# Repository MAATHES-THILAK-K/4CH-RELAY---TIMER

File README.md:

# 4CH Relay Timer

## Overview
ESP32-C3 based 4-channel relay controller with DS3231 RTC for timer applications. Each channel handles 10A AC loads with MOSFET input control.

## Features
- 4x 10A relays with MOSFET control
- ESP32-C3 Mini for Wi-Fi/Bluetooth
- DS3231 RTC for precise timing
- Direct AC input sensing
- Timer-based automation

## Hardware
- MCU: ESP32-C3-MINI-1
- RTC: DS3231 with battery backup
- Relays: 10A 250VAC SPDT
- Input: 5V DC
- AC sensing: Opto-isolated

## Usage
1. Power with 5V DC
2. Connect AC loads to relay outputs
3. Program via USB-C
4. Set timers via web interface

## Safety
⚠️ **HIGH VOLTAGE** - Requires proper insulation and qualified installation.

## License
Apache 2.0

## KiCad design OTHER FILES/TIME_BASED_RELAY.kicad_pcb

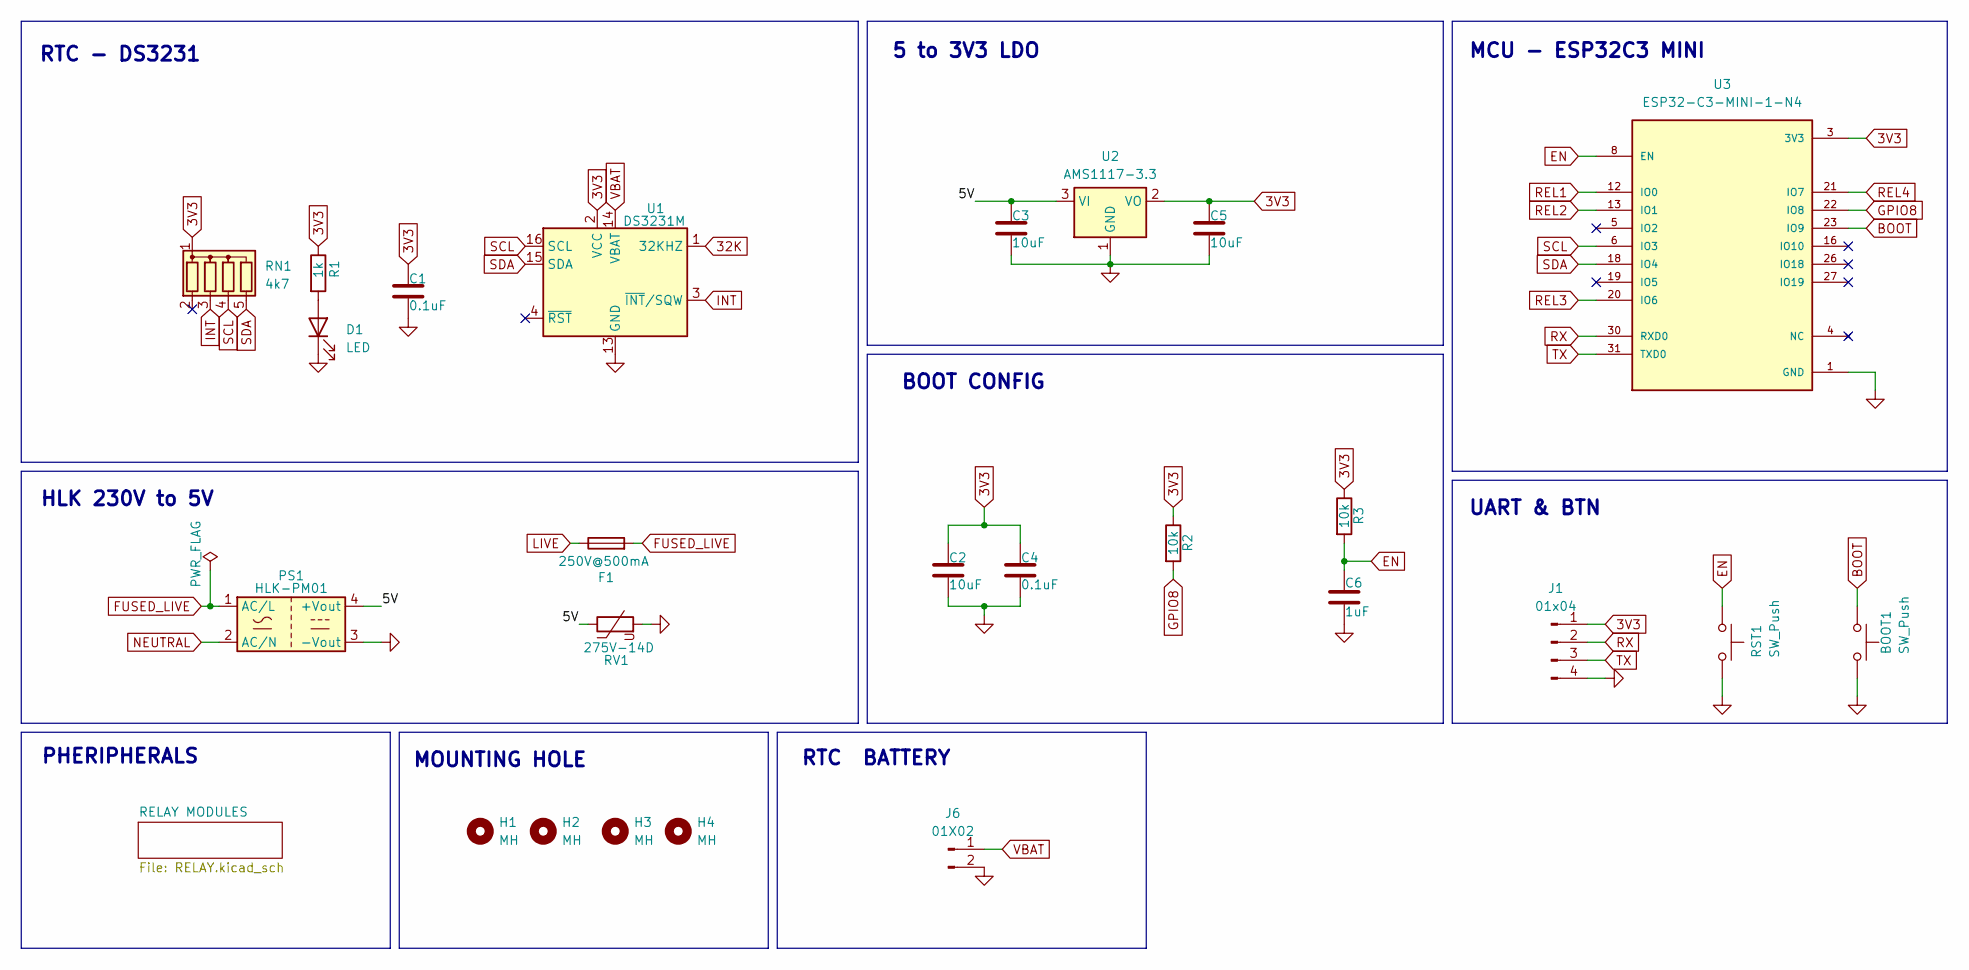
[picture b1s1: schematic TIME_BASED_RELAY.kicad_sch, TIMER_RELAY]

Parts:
BOOT1: SW_Push; SW_Tactile_SPST_NO_Straight_CK_PTS636Sx25SMTRLFS
C1, C4: 0.1uF; C_0805_2012Metric_Pad1.18x1.45mm_HandSolder
C2, C3, C5: 10uF; C_0805_2012Metric_Pad1.18x1.45mm_HandSolder
C6: 1uF; C_0805_2012Metric_Pad1.18x1.45mm_HandSolder
D1: LED; LED_0805_2012Metric_Pad1.15x1.40mm_HandSolder
F1: 250V@500mA; Fuseholder_Clip-6.3x32mm_Littelfuse_102_122_Inline_P34.21x7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
H1, H2, H3, H4: MH; MountingHole_2.2mm_M2_Pad_Via
J1: 01x04; JST_SH_SM04B-SRSS-TB_1x04-1MP_P1.00mm_Horizontal
J6: 01X02; BatteryHolder_Keystone_1058_1x2032
PS1: HLK-PM01; Converter_ACDC_Hi-Link_HLK-PMxx
R1: 1k; R_0805_2012Metric_Pad1.20x1.40mm_HandSolder
R2, R3: 10k; R_0805_2012Metric_Pad1.20x1.40mm_HandSolder
RN1: 4k7; R_Array_SIP5
RST1: SW_Push; SW_Tactile_SPST_NO_Straight_CK_PTS636Sx25SMTRLFS
RV1: 275V-14D; RV_Disc_D15.5mm_W7.5mm_P7.5mm
U1: DS3231M; SOIC-16W_7.5x10.3mm_P1.27mm
U2: AMS1117-3.3; SOT-223-3_TabPin2
U3: ESP32-C3-MINI-1-N4; XCVR_ESP32-C3-MINI-1-N4; PARTREV v1.0

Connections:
3V3: C1.1, C2.1, C4.1, C5.1, J1.1, R1.1, R2.1, R3.1, RN1.1 (common), U1.2 (VCC), U2.2 (VO), U3.3 (3V3)
32K: U1.1 (32KHZ)
/5V: C3.1, PS1.4 (+Vout), RV1.1, U2.3 (VI)
BOOT: BOOT1.1, U3.23 (IO9)
EN: C6.1, R3.2, RST1.1, U3.8 (EN); also elsewhere on the board
FUSED_LIVE: F1.2, PS1.1 (AC/L)
GND: BOOT1.2, C1.2, C2.2, C3.2, C4.2, C5.2, C6.2, D1.1 (K), J1.4, J6.2, PS1.3 (-Vout), RST1.2, RV1.2, U1.5 (GND), U1.6 (GND), U1.7 (GND), U1.8 (GND), U1.9 (GND), U1.10 (GND), U1.11 (GND), U1.12 (GND), U1.13 (GND), U2.1 (GND), U3.1 (GND), U3.2 (GND), U3.11 (GND), U3.14 (GND), U3.36 (GND), U3.37 (GND), U3.38 (GND), U3.39 (GND), U3.40 (GND), U3.41 (GND), U3.42 (GND), U3.43 (GND), U3.44 (GND), U3.45 (GND), U3.46 (GND), U3.47 (GND), U3.48 (GND), U3.49_1 (GND), U3.49_2 (GND), U3.49_3 (GND), U3.49_4 (GND), U3.49_5 (GND), U3.49_6 (GND), U3.49_7 (GND), U3.49_8 (GND), U3.49_9 (GND), U3.50 (GND), U3.51 (GND), U3.52 (GND), U3.53 (GND); also elsewhere on the board
GPIO8: R2.2, U3.22 (IO8)
INT: RN1.3 (R2), U1.3 (~INT/SQW)
LIVE: F1.1; also elsewhere on the board
NEUTRAL: PS1.2 (AC/N); also elsewhere on the board
unnamed: D1.2 (A), R1.2
REL1: U3.12 (IO0); also elsewhere on the board
REL2: U3.13 (IO1); also elsewhere on the board
REL3: U3.20 (IO6); also elsewhere on the board
REL4: U3.21 (IO7); also elsewhere on the board
RX: J1.2, U3.30 (RXD0)
SCL: RN1.4 (R3), U1.16 (SCL), U3.6 (IO3)
SDA: RN1.5 (R4), U1.15 (SDA), U3.18 (IO4)
TX: J1.3, U3.31 (TXD0)
VBAT: J6.1, U1.14 (VBAT)

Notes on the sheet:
PHERIPHERALS
HLK 230V to 5V
RTC BATTERY
MOUNTING HOLE
UART & BTN
BOOT CONFIG
MCU - ESP32C3 MINI
RTC - DS3231
5 to 3V3 LDO

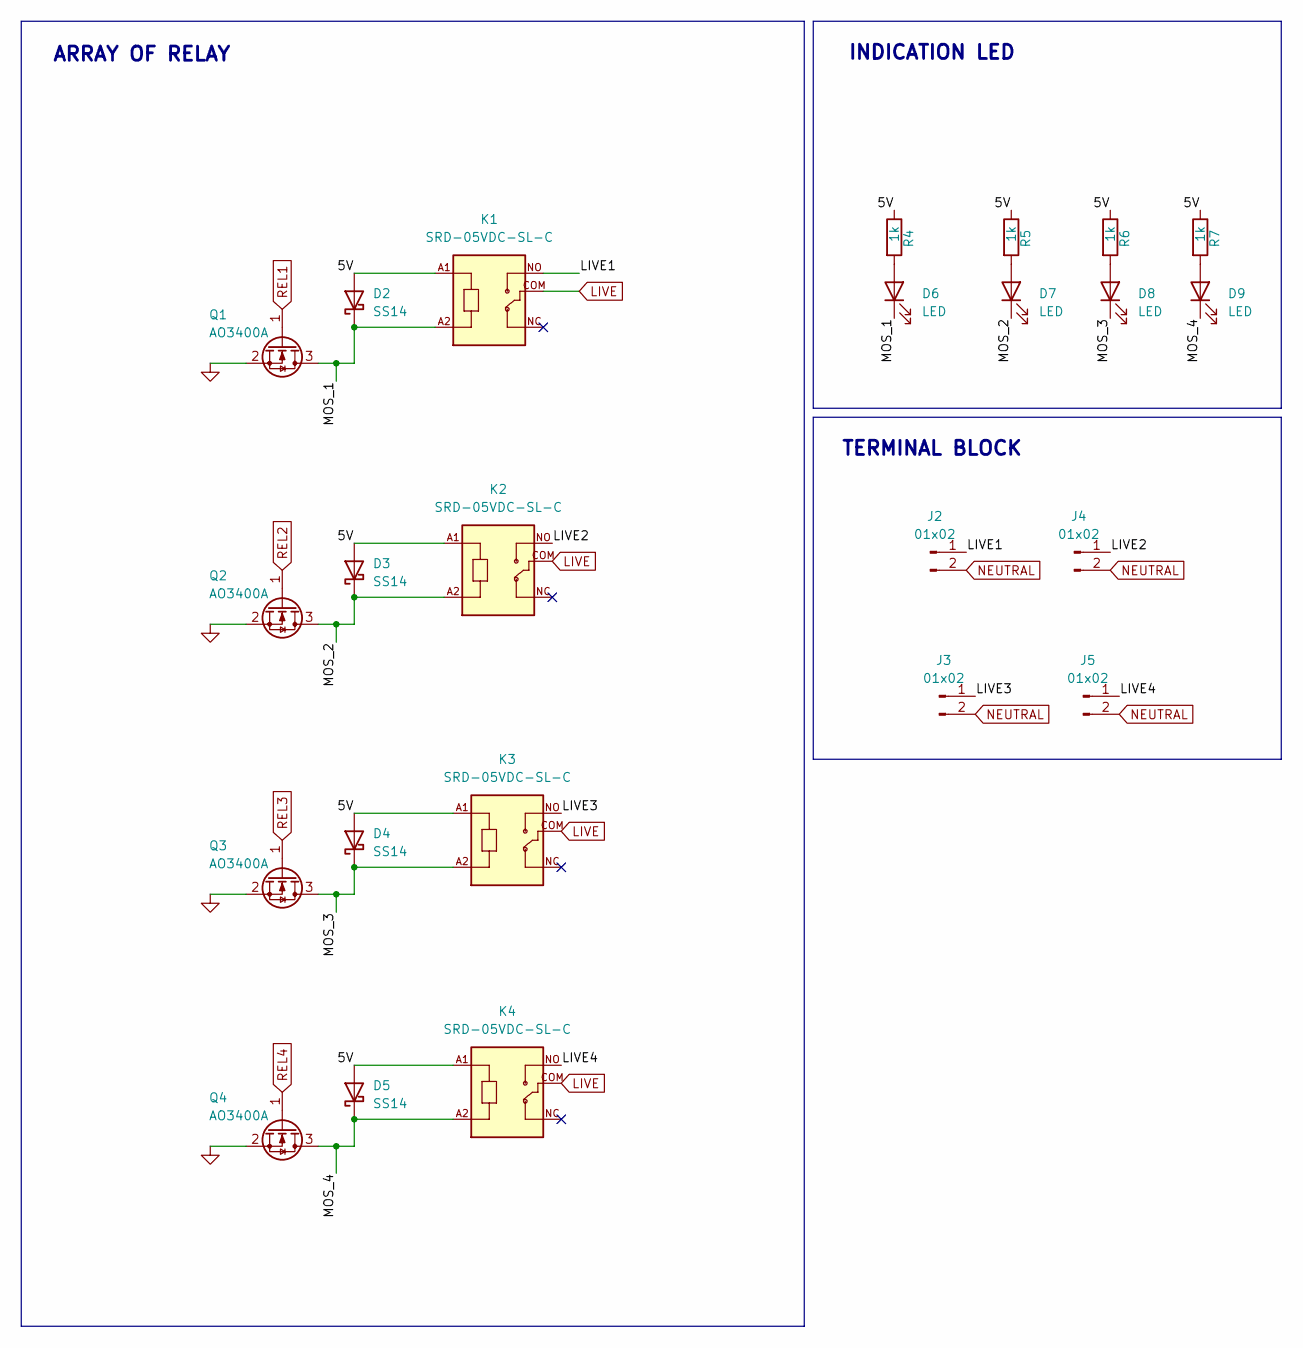
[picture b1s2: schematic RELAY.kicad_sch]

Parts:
D2, D3, D4, D5: SS14; D_SMA
D6, D7, D8, D9: LED; LED_0805_2012Metric_Pad1.15x1.40mm_HandSolder
J2, J3, J4, J5: 01x02; TerminalBlock_MaiXu_MX126-5.0-02P_1x02_P5.00mm
K1, K2, K3, K4: SRD-05VDC-SL-C; RELAY_SRD-05VDC-SL-C
Q1, Q2, Q3, Q4: AO3400A; SOT-23
R4, R5, R6, R7: 1k; R_0805_2012Metric_Pad1.20x1.40mm_HandSolder

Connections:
/RELAY MODULES/5V: D2.2 (A), D3.2 (A), D4.2 (A), D5.2 (A), K1.A1, K2.A1, K3.A1, K4.A1, R4.1, R5.1, R6.1, R7.1
/RELAY MODULES/LIVE1: J2.1, K1.NO
/RELAY MODULES/LIVE2: J4.1, K2.NO
/RELAY MODULES/LIVE3: J3.1, K3.NO
/RELAY MODULES/LIVE4: J5.1, K4.NO
/RELAY MODULES/MOS_1: D2.1 (K), D6.1 (K), K1.A2, Q1.3 (D)
/RELAY MODULES/MOS_2: D3.1 (K), D7.1 (K), K2.A2, Q2.3 (D)
/RELAY MODULES/MOS_3: D4.1 (K), D8.1 (K), K3.A2, Q3.3 (D)
/RELAY MODULES/MOS_4: D5.1 (K), D9.1 (K), K4.A2, Q4.3 (D)
GND: Q1.2 (S), Q2.2 (S), Q3.2 (S), Q4.2 (S); also elsewhere on the board
LIVE: K1.COM, K2.COM, K3.COM, K4.COM; also elsewhere on the board
NEUTRAL: J2.2, J3.2, J4.2, J5.2; also elsewhere on the board
unnamed: D6.2 (A), R4.2
unnamed: D7.2 (A), R5.2
unnamed: D8.2 (A), R6.2
unnamed: D9.2 (A), R7.2
REL1: Q1.1 (G); also elsewhere on the board
REL2: Q2.1 (G); also elsewhere on the board
REL3: Q3.1 (G); also elsewhere on the board
REL4: Q4.1 (G); also elsewhere on the board

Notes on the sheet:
ARRAY OF RELAY
INDICATION LED
TERMINAL BLOCK

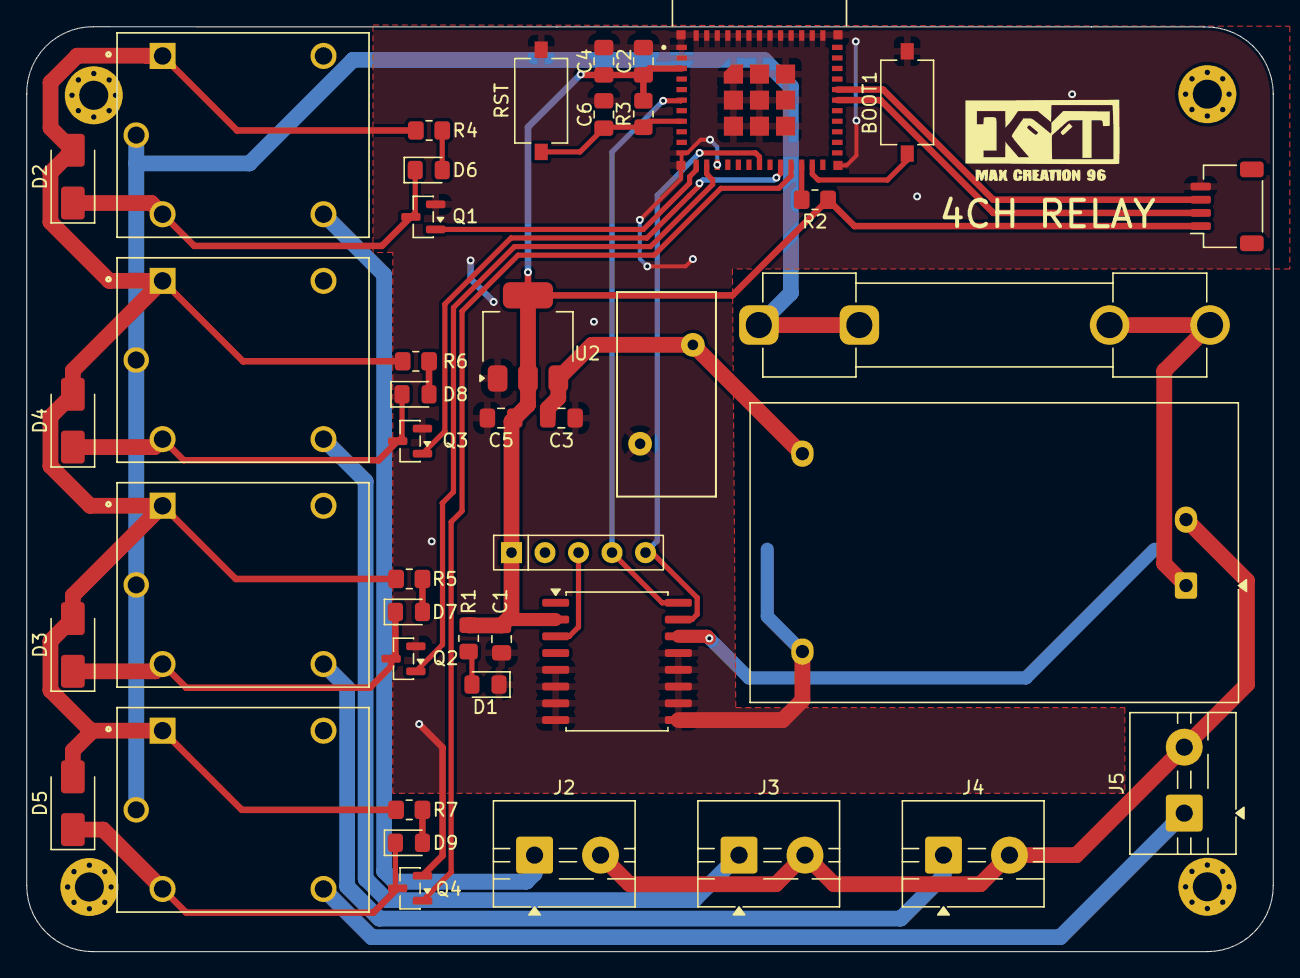
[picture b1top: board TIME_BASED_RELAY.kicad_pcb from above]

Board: 2 copper layers, 94.5 x 70.1 mm, 49 parts (1 on the bottom side), 33 nets.

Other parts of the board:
RST: SW_Push; SW_Tactile_SPST_NO_Straight_CK_PTS636Sx25SMTRLFS

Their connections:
EN: RST.1; also elsewhere on the board
GND: RST.2; also elsewhere on the board

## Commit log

2026-01-29 Update LICENSE
2026-01-29 Create TEMP
